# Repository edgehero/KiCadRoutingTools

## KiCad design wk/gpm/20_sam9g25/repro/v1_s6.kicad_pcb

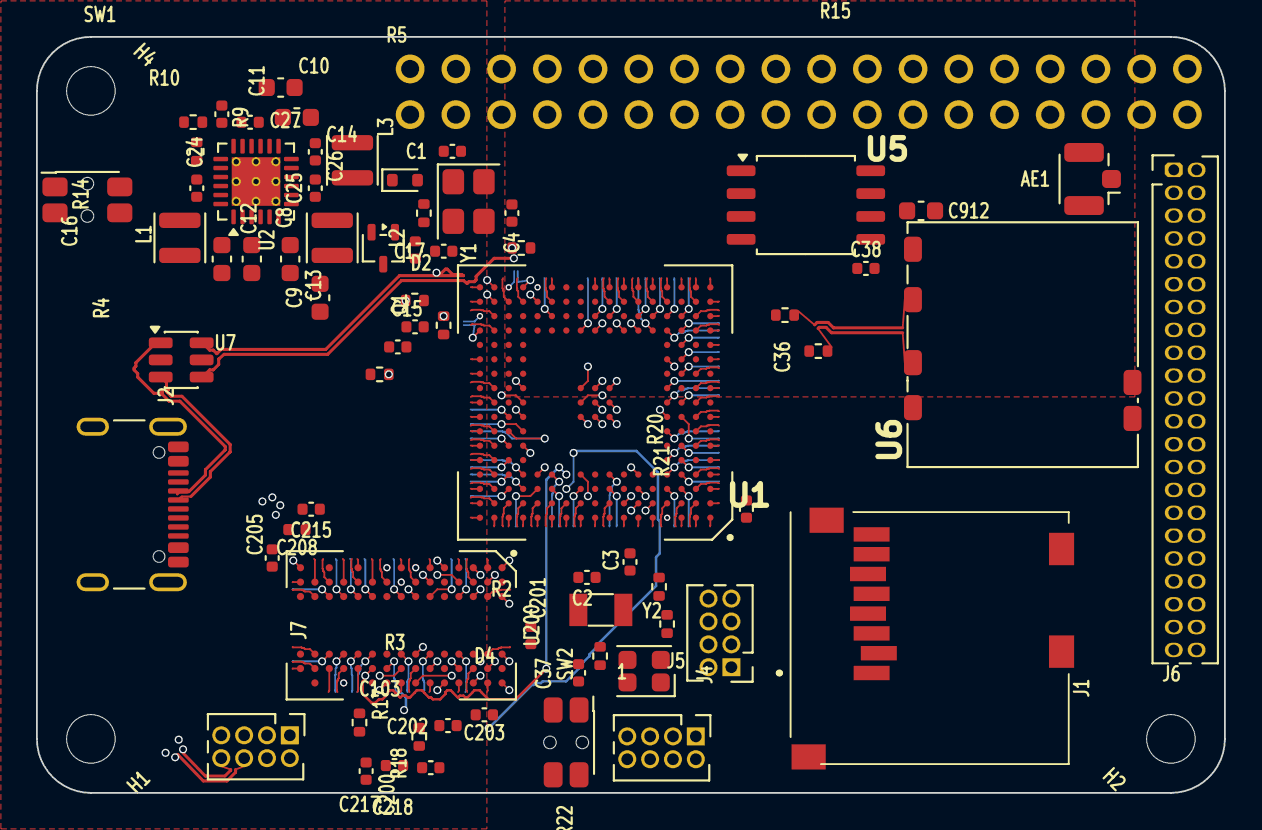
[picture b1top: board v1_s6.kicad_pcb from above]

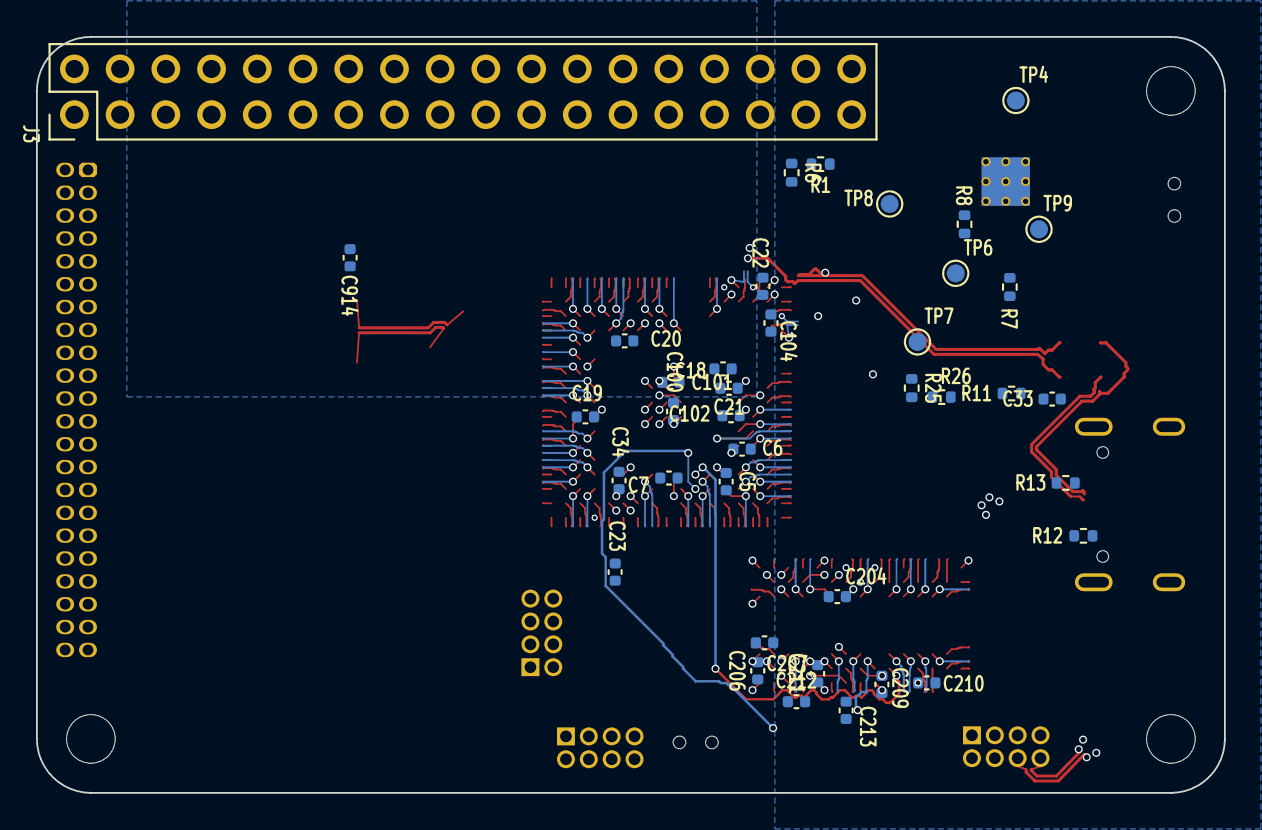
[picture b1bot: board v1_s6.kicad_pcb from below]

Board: 4 copper layers, 66.0 x 42.0 mm, 111 parts (39 on the bottom side), 156 nets.

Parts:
AE1: Antenna_Shield; U.FL_Hirose_U.FL-R-SMT-1_Vertical
C1, C4: 22pF; C_0402_1005Metric
C2, C3: 12pF; C_0402_1005Metric
C5, C6, C7, C17, C18, C19, C20, C21, C22, C23, C24, C25, C26, C27, C100, C101, C102, C103, C104: 220nF; C_0402_1005Metric
C8, C9, C10, C12, C13, C14, C912: 10uF; C_0603_1608Metric
C11, C15: 2.2uF; C_0402_1005Metric
C16: 10pF; C_0402_1005Metric
C33, C34, C38, C200, C201, C202, C203, C204, C205, C206, C207, C208, C209, C210, C211, C212, C213, C215, C217, C218, C914: 100nF; C_0402_1005Metric
C36, C37: 1uF; C_0402_1005Metric
D2: D_Schottky; D_SOD-523
D4: LED_BAGR; LED_RGB_Optosupply_OSTB0805C1E-A-0.8T
H1, H2, H4: MountingHole; MountingHole_2.7mm
J1: Micro_SD_Card_Det; MEM20610118800A
J2: USB_C_Receptacle_USB2.0_16P; USB_C_Receptacle_GCT_USB4105-xx-A_16P_TopMnt_Horizontal
J3: Conn_02x18_Odd_Even; PinHeader_2x18_P2.54mm_Vertical
J4, J5, J7: Conn_01x08; PinHeader_2x04_P1.27mm_Vertical
J6: Conn_02x22_Odd_Even; PinHeader_2x22_P1.27mm_Vertical
L1, L2, L3: 2.2uH; L_Wuerth_MAPI-2512
Q1: BSS84; SOT-323_SC-70
R1, R6, R8, R25, R26: 68k; R_0402_1005Metric
R2, R3, R4, R5, R15, R16: 39; R_0402_1005Metric
R7: 1M; R_0402_1005Metric
R9: 22k; R_0402_1005Metric
R10: 191k; R_0402_1005Metric
R11: 2.2K; R_0402_1005Metric
R12, R13: 5.1K; R_0402_1005Metric
R14: 6k8; R_0402_1005Metric
R17, R18: 2.2k; R_0402_1005Metric
R20, R21, R22: 180; R_0402_1005Metric
SW1, SW2: SW_SPST; SW_SPST_EVQP7C
TP4, TP6, TP7, TP8, TP9: TestPoint; TestPoint_Pad_D1.0mm
U1: AT91SAM9G15; AT91SAM9G10
U2: MCP16501A; QFN-24-1EP_4x4mm_P0.5mm_EP2.7x2.7mm_ThermalVias
U5: W25Q128JVS; SOIC-8_5.23x5.23mm_P1.27mm
U6: RTL8188CUS
U7: USBLC6-2P6; SOT-23-6
U200: DDR2-x16; BGA-84_9x15_8.0x12.5mm
Y1: 12MHz; Crystal_SMD_3225-4Pin_3.2x2.5mm
Y2: 32.768kHz; Crystal_SMD_3215-2Pin_3.2x1.5mm

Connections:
+1V0_LDO: C11.1, C15.1, C103.1, C104.1, R9.1, U1.R12 (VDDPLLA), U1.T17 (VDDUTMIC), U2.18 (LOUT)
/IO expansions/cc1: J2.A5 (CC1), R13.1
/IO expansions/cc2: J2.B5 (CC2), R12.1
/IO expansions/usb-a+: J2.A6 (D+), J2.B6 (D+), U7.3 (I/O2)
/IO expansions/usb-a-: J2.A7 (D-), J2.B7 (D-), U7.1 (I/O1)
/cpu/hse_in: C1.1, U1.T12 (XIN), Y1.1
/cpu/hse_out: C4.1, U1.U12 (XOUT), Y1.3
/cpu/lse_in: C2.1, U1.A6 (XIN32), Y2.1
/cpu/lse_out: C3.1, U1.A5 (XOUT32), Y2.2
/memory/ddr-a2: U1.H15 (A2), U200.M8 (A0)
/memory/ddr-a3: U1.H17 (A3), U200.M3 (A1)
/memory/ddr-a4: U1.G17 (A4), U200.M7 (A2)
/memory/ddr-a5: U1.G16 (A5), U200.N2 (A3)
/memory/ddr-a6: U1.F17 (A6), U200.N8 (A4)
/memory/ddr-a7: U1.E17 (A7), U200.N3 (A5)
/memory/ddr-a8: U1.F16 (A8), U200.N7 (A6)
/memory/ddr-a9: U1.G15 (A9), U200.P2 (A7)
/memory/ddr-a10: U1.G14 (A10), U200.P8 (A8)
/memory/ddr-a11: U1.F15 (A11), U200.P3 (A9)
/memory/ddr-a13: U1.C17 (A13), U200.P7 (A11)
/memory/ddr-a14: U1.E16 (A14), U200.R2 (A12)
/memory/ddr-a15: U1.D16 (A15), U200.R8 (A13)
/memory/ddr-ba0: U1.C16 (A16/BA0), U200.L2 (BA0)
/memory/ddr-ba1: U1.B17 (A17/BA1), U200.L3 (BA1)
/memory/ddr-ba2: U1.E15 (A18), U200.L1 (BA2)
/memory/ddr-cas: U1.C10 (CAS), U200.L7 (~CAS)
/memory/ddr-ck+: U1.C11 (~SDCK), U200.J8 (CK)
/memory/ddr-ck-: U1.D11 (SDCK), U200.K8 (~CK)
/memory/ddr-cke: U1.B12 (SDCKE), U200.K2 (CKE)
/memory/ddr-cs: U1.B8 (NCS1/SDCS), U200.L8 (~CS)
/memory/ddr-d0: U1.D14 (D0), U200.G8 (DQ0)
/memory/ddr-d1: U1.D15 (D1), U200.H3 (DQ3)
/memory/ddr-d2: U1.A16 (D2), U200.F1 (DQ6)
/memory/ddr-d3: U1.B16 (D3), U200.G2 (DQ1)
/memory/ddr-d4: U1.A17 (D4), U200.H1 (DQ4)
/memory/ddr-d5: U1.B15 (D5), U200.H7 (DQ2)
/memory/ddr-d6: U1.C14 (D6), U200.H9 (DQ5)
/memory/ddr-d7: U1.B14 (D7), U200.F9 (DQ7)
/memory/ddr-d8: U1.A15 (D8), U200.D1 (DQ12)
/memory/ddr-d9: U1.C15 (D9), U200.B1 (DQ14)
/memory/ddr-d10: U1.D12 (D10), U200.B9 (DQ15)
/memory/ddr-d11: U1.C13 (D11), U200.D3 (DQ11)
/memory/ddr-d12: U1.A14 (D12), U200.C2 (DQ9)
/memory/ddr-d13: U1.B13 (D13), U200.D7 (DQ10)
/memory/ddr-d14: U1.A13 (D14), U200.C8 (DQ8)
/memory/ddr-d15: U1.C12 (D15), U200.D9 (DQ13)
/memory/ddr-dqm0: U1.A10 (DQM0), U200.F3 (LDM)
/memory/ddr-dqm1: U1.B10 (DQM1), U200.B3 (UDM)
/memory/ddr-dqs0: U1.A11 (DQS0), U200.F7 (LDQS)
/memory/ddr-dqs1: U1.A9 (DQS1), U200.B7 (UDQS)
/memory/ddr-ras: U1.B11 (RAS), U200.K7 (~RAS)
/memory/ddr-sda10: U1.C8 (SDA10), U200.M2 (A10/AP)
/memory/ddr-sdwe: U1.A12 (SDWE), U200.K3 (~WE)
/power/vbg: C16.1, R14.1, U1.U17 (VBG)
ACIN: D2.2 (A), J3.3, Q1.1 (G), R1.1
AC_DET: R1.2, R6.1, U1.T7 (PA24)
BTN_USR: C37.1, SW2.1 (A), U1.J17 (PD19)
CAN0-RX: J3.30, U1.R4 (PA6)
CAN0-TX: J3.29, U1.R1 (PA5)
DDR_VREF: C200.1, C217.2, C218.1, R17.2, R18.1, U200.J2 (VREF)
GND: AE1.2 (Shield), C1.2, C2.2, C3.2, C4.2, C5.2, C6.2, C7.2, C8.2, C9.2, C10.2, C11.2, C12.2, C13.2, C14.2, C15.2, C16.2, C17.2, C18.2, C19.2, C20.2, C21.2, C22.2, C23.2, C24.2, C25.2, C26.2, C27.2, C33.2, C34.2, C36.2, C37.2, C38.2, C100.2, C101.2, C102.2, C103.2, C104.2, C200.2, C201.2, C202.2, C203.2, C204.2, C205.2, C206.2, C207.2, C208.2, C209.2, C210.2, C211.2, C212.2, C213.2, C215.2, C218.2, C912.2, C914.2, J1.G1 (SHIELD), J1.G2 (SHIELD), J1.P6 (VSS), J2.A1 (GND), J2.A12 (GND), J2.B1 (GND), J2.B12 (GND), J2.SH (SHIELD), J3.1, J3.14, J3.23, J3.36, J4.1, J5.1, J6.1, J6.10, J6.11, J6.36, J6.37, J6.44, J7.1, J7.7, R6.2, R10.2, R11.2, R12.2, R13.2, R14.2, R18.2, R26.2, SW1.2 (B), SW2.2 (B), TP4.1 (1_1), U1.B6 (GNDBU), U1.B7 (TST), U1.D6 (GNDANA), U1.H8 (GNDCORE), U1.H9 (GNDIOM), U1.H10 (GNDIOM), U1.J8 (GNDCORE), U1.J9 (GNDIOM), U1.J10 (GNDIOM), U1.J14 (VDDNF), U1.K10 (GNDCORE), U1.M4 (GNDIOP), U1.P6 (GNDIOP), U1.T16 (GNDUTMI), U1.U13 (GNDOSC), U2.4 (LPM), U2.9 (PGND2), U2.10 (PGND3), U2.15 (SELv3), U2.16 (SGND), U2.22 (PGND1), U2.25 (EP), U5.4 (GND), U6.1 (GND), U6.5 (GND), U7.2 (GND), U200.A3 (VSS), U200.A7 (VSSQ), U200.B2 (VSSQ), U200.B8 (VSSQ), U200.D2 (VSSQ), U200.D8 (VSSQ), U200.E3 (VSS), U200.E7 (VSSQ), U200.F2 (VSSQ), U200.F8 (VSSQ), U200.H2 (VSSQ), U200.H8 (VSSQ), U200.J3 (VSS), U200.J7 (VSSDL), U200.K9 (ODT), U200.N1 (VSS), U200.P9 (VSS)
GPIO1: J3.13, U1.T8 (PA25)
GPIO2: J3.20, U1.J16 (PD21)
GPIO3: J3.19, U1.U8 (PA28)
GPIO4: J3.24, U1.K16 (PD20)
GPIOA1: J3.31, U1.A2 (PB13)
GPIOA2: J3.32, U1.C4 (PB14)
GPIOA3: J3.33, U1.C3 (PB15)
GPIOA4: J3.34, U1.A1 (PB16)
GPIOA5: J3.35, U1.B1 (PB17)
I2C-SCL: J3.17, J6.6, U1.U9 (PA31)
I2C-SDA: J3.18, J6.7, U1.R8 (PA30)
LCD-CLK: J6.39, U1.R2 (PC30)
LCD-D2: J6.33, U1.F3 (PC2)
LCD-D3: J6.32, U1.H2 (PC3)
LCD-D4: J6.31, U1.E1 (PC4)
LCD-D5: J6.30, U1.G4 (PC5)
LCD-D6: J6.29, U1.F2 (PC6)
LCD-D7: J6.28, U1.F1 (PC7)
LCD-D10: J6.25, U1.G2 (PC10)
LCD-D11: J6.24, U1.H3 (PC11)
LCD-D12: J6.23, U1.J3 (PC12)
LCD-D13: J6.22, U1.L2 (PC13)
LCD-D14: J6.21, U1.H1 (PC14)
LCD-D15: J6.20, U1.J2 (PC15)
LCD-D18: J6.17, U1.K2 (PC18)
LCD-D19: J6.16, U1.N3 (PC19)
LCD-D20: J6.15, U1.K1 (PC20)
LCD-D21: J6.14, U1.M3 (PC21)
LCD-D22: J6.13, U1.P3 (PC22)
LCD-D23: J6.12, U1.J4 (PC23)
LCD-DE: J6.38, U1.N1 (PC29)
LCD-HSYNC: J6.40, U1.K4 (PC28)
LCD-PWM: J6.42, U1.P2 (PC26)
LCD-VSYNC: J6.41, U1.M1 (PC27)
LED-BLUE: R22.1, U1.T6 (PA21)
LED-GREEN: R21.1, U1.A3 (PB11)
LED-RED: R20.1, U1.B4 (PB12)
MCI0-CK: J1.P5 (CLK), U1.R5 (PA17)
MCI0-D0: J1.P7 (DAT0), U1.U4 (PA15)
MCI0-D1: J1.P8 (DAT1), U1.U5 (PA18)
MCI0-D2: J1.P1 (DAT2), U1.T5 (PA19)
MCI0-D3: J1.P2 (DAT3/CD), U1.U6 (PA20)
MCI0-DC: J1.P3 (CMD), U1.P5 (PA16)
MCI0-DET: J1.CD1 (DET_A), J1.CD2 (DET_B), U1.R9 (PA29)
unnamed: AE1.1 (A), U6.6 (ANT)
unnamed: D4.1 (BK), R22.2
unnamed: D4.3 (GK), R21.2
unnamed: D4.4 (RK), R20.2
unnamed: R3.2, U1.T15 (HFSDMA)
unnamed: R5.2, U1.P16 (HFSDMB)
unnamed: R16.2, U1.M17 (HFSDMC)
unnamed: R2.2, U1.T14 (HFSDPA)
unnamed: R4.2, U1.R16 (HFSDPB)
unnamed: R15.2, U1.L17 (HFSDPC)
unnamed: R9.2, R10.1, U2.19 (LFB)
unnamed: L1.1, U2.23 (SW1)
unnamed: L2.1, U2.8 (SW2)
unnamed: L3.1, U2.11 (SW3)
PWR_BTN: SW1.1 (A), U2.14 (~STRT)
RMII-MDC: J4.8, U1.B3 (PB6)
RMII-MDIO: J5.8, U1.E3 (PB5)
RMII-RX0: J4.4, U1.D3 (PB0)
RMII-RX1: J4.5, U1.D4 (PB1)
RMII-RXDV: J4.2, U1.E4 (PB3)
RMII-RXER: J4.3, U1.D2 (PB2)
RMII-TX0: J5.4, U1.C1 (PB9)
RMII-TX1: J5.5, U1.B2 (PB10)
RMII-TXCK: J5.2, U1.D1 (PB4)
RMII-TXEN: J5.3, U1.C2 (PB7)
SHDN: R7.2, U1.D8 (SHDN), U2.3 (PWRHLD)
SPI0-CLK: J3.25, U1.T4 (PA13), U5.6 (CLK)
SPI0-CS0: U1.U2 (PA14), U5.1 (~CS)
SPI0-MISO: J3.28, U1.U1 (PA11), U5.5 (DI(IO0))
SPI0-MOSI: J3.27, U1.T2 (PA12), U5.2 (DO(IO1))
SPI-CS: J3.26, U1.R6 (PA22)
UART0-RX: J3.12, U1.U3 (PA9)
UART0-TX: J3.11, U1.T1 (PA10)
UART1-RX: J3.16, U1.P4 (PA8)
UART1-TX: J3.15, U1.R3 (PA7)
UART2-RX: J3.22, U1.P1 (PA1)
UART2-TX: J3.21, U1.L3 (PA0)
USB0-D+: R2.1, U1.U14 (HHSDPA), U7.4 (I/O2)
USB0-D-: R3.1, U1.U15 (HHSDMA), U7.6 (I/O1)
USB1-D+: R15.1, U6.2 (USB_DP)
USB1-D-: R16.1, U6.3 (USB_DM)
USB2-D+: J7.8, R4.1, U1.R17 (HHSDPB)
USB2-D-: J7.6, R5.1, U1.P17 (HHSDMB)
USB_DET: R25.2, R26.1, U1.U7 (PA23)
VBUS: C33.1, J2.A4 (VBUS), J2.A9 (VBUS), J2.B4 (VBUS), J2.B9 (VBUS), Q1.3 (D), R11.1, R25.1, U7.5 (VBUS)
VDD-IO: C8.1, C12.1, C17.1, C18.1, C19.1, C20.1, C21.1, C22.1, C23.1, C34.1, C36.1, C38.1, C912.1, C914.1, D4.2 (A), J1.P4 (VDD), J3.2, J6.8, J6.43, L1.2, R7.1, R8.1, TP9.1 (1_1), U1.A4 (ADVREF), U1.B5 (VDDBU), U1.C6 (VDDANA), U1.H4 (VDDIOP1), U1.K14 (VDDNF), U1.P7 (VDDIOP0), U1.P9 (BMS), U1.T13 (VDDOSC), U1.U16 (VDDUTMII), U2.1 (OUT1), U5.8 (VCC), U6.4 (+3V3)
VDD_CORE: C10.1, C14.1, C100.1, C101.1, C102.1, L3.2, TP7.1 (1_1), U1.H14 (VDDCORE), U1.K8 (VDDCORE), U1.K9 (VDDCORE), U2.13 (OUT3)
VDD_DDR: C5.1, C6.1, C7.1, C9.1, C13.1, C201.1, C202.1, C203.1, C204.1, C205.1, C206.1, C207.1, C208.1, C209.1, C210.1, C211.1, C212.1, C213.1, C215.1, C217.1, L2.2, R17.1, TP6.1 (1_1), U1.D10 (VDDIOM), U1.D13 (VDDIOM), U1.F14 (VDDIOM), U2.6 (OUT2), U200.A1 (VDD), U200.A9 (VDDQ), U200.C1 (VDDQ), U200.C3 (VDDQ), U200.C7 (VDDQ), U200.C9 (VDDQ), U200.E1 (VDD), U200.E9 (VDDQ), U200.G1 (VDDQ), U200.G3 (VDDQ), U200.G7 (VDDQ), U200.G9 (VDDQ), U200.J1 (VDDL), U200.J9 (VDD), U200.M9 (VDD), U200.R1 (VDD)
VIN: C24.1, C25.1, C26.1, C27.1, D2.1 (K), Q1.2 (S), TP8.1 (1_1), U2.7 (PVIN2), U2.12 (PVIN3), U2.17 (VIN), U2.20 (SELv2), U2.21 (LEN), U2.24 (PVIN1)
WKUP: R8.2, U1.A7 (WKUP), U2.5 (~STRTO)
~RST: J3.7, U1.P10 (NRST), U2.2 (~RSTO)

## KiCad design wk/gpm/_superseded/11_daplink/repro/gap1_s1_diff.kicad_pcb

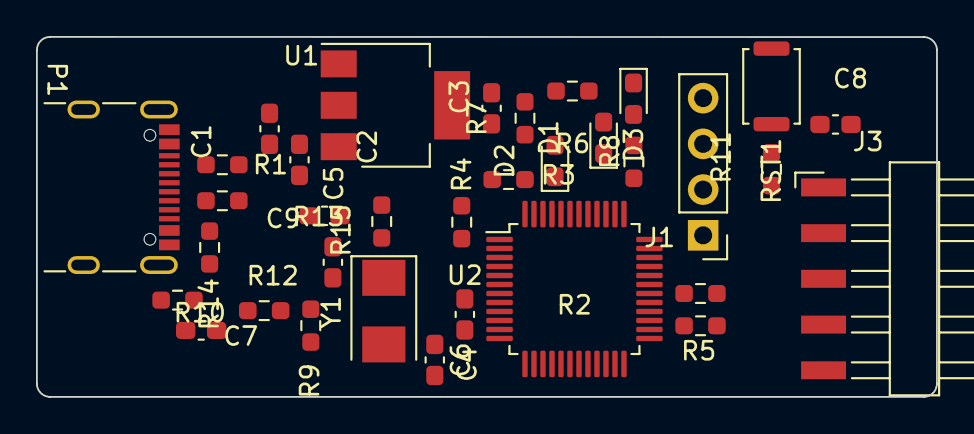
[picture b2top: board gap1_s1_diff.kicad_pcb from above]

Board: 2 copper layers, 50.0 x 20.0 mm, 35 parts (1 on the bottom side), 29 nets, no tracks yet.

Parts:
C1, C4, C8: 10nF; C_0603_1608Metric_Pad1.08x0.95mm_HandSolder
C2, C3: 10uF; C_0603_1608Metric_Pad1.08x0.95mm_HandSolder
C5, C6: 20pF; C_0603_1608Metric_Pad1.08x0.95mm_HandSolder
C7, C9: 18pF; C_0603_1608Metric_Pad1.08x0.95mm_HandSolder
D1: LEDG; LED_0603_1608Metric_Pad1.05x0.95mm_HandSolder
D2: LEDB; LED_0603_1608Metric_Pad1.05x0.95mm_HandSolder
D3: LEDR; LED_0603_1608Metric_Pad1.05x0.95mm_HandSolder
J1: Conn_01x04; PinHeader_1x04_P2.54mm_Vertical
J2, J3: Conn_01x05; Harwin_M20-89005xx_1x05_P2.54mm_Horizontal
P1: USB_C_Receptacle_USB2.0; USB_C_Receptacle_GCT_USB4105-xx-A_16P_TopMnt_Horizontal
R1, R14: 5K1; R_0603_1608Metric_Pad0.98x0.95mm_HandSolder
R2, R3, R4, R11: 10K; R_0603_1608Metric_Pad0.98x0.95mm_HandSolder
R5: 100; R_0603_1608Metric_Pad0.98x0.95mm_HandSolder
R6, R7, R15: 1K5; R_0603_1608Metric_Pad0.98x0.95mm_HandSolder
R8: 470; R_0603_1608Metric_Pad0.98x0.95mm_HandSolder
R9, R10: 4K7; R_0603_1608Metric_Pad0.98x0.95mm_HandSolder
R12, R13: 33; R_0603_1608Metric_Pad0.98x0.95mm_HandSolder
RST1: RST; SW_Push_SPST_NO_Alps_SKRK
U1: AMS1117-3.3; SOT-223-3_TabPin2
U2: STM32F103CBTx; LQFP-48_7x7mm_P0.5mm
Y1: 8MHz; Crystal_SMD_5032-2Pin_5.0x3.2mm

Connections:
+3.3V: C3.1, J1.1, J2.5, J3.1, R2.1, R6.1, R7.1, R9.1, R11.1, R15.2, U1.2 (VO), U2.1 (VBAT), U2.9 (VDDA), U2.24 (VDD), U2.36 (VDD), U2.48 (VDD)
+5V: C1.1, C2.1, P1.A4 (VBUS), P1.A9 (VBUS), P1.B4 (VBUS), P1.B9 (VBUS), U1.3 (VI)
/D+: P1.A6 (D+), P1.B6 (D+), R13.2
/D-: P1.A7 (D-), P1.B7 (D-), R12.2
/IF_RST: C4.1, R2.2, U2.7 (NRST)
/IF_SWCLK: J1.3, U2.37 (PA14)
/IF_SWDIO: J1.2, U2.34 (PA13)
/OSCIN: C5.1, U2.5 (PD0), Y1.1
/OSCOUT: C6.1, U2.6 (PD1), Y1.2
/PA0: R9.2, R10.1, U2.10 (PA0)
/PA9: R8.1, U2.30 (PA9)
/PA11: C7.1, R12.1, U2.32 (PA11)
/PA12: C9.1, R13.1, R15.1, U2.33 (PA12)
/PB5: D1.1 (K), U2.41 (PB5)
/PB6: D2.1 (K), U2.42 (PB6)
/TGT_RST: C8.1, J3.4, R11.2, RST1.1, U2.18 (PB0)
/TGT_RX: J2.3, U2.12 (PA2)
/TGT_SWCLK: J3.3, U2.15 (PA5), U2.26 (PB13)
/TGT_SWDIO: J3.2, R5.1, U2.27 (PB14)
/TGT_TX: J2.4, U2.13 (PA3)
GND: C1.2, C2.2, C3.2, C4.2, C5.2, C6.2, C7.2, C8.2, C9.2, D3.1 (K), J1.4, J2.1, J3.5, P1.A1 (GND), P1.A12 (GND), P1.B1 (GND), P1.B12 (GND), P1.S1 (SHIELD), R1.2, R3.1, R4.1, R10.2, R14.2, RST1.2, U1.1 (GND), U2.8 (VSSA), U2.20 (PB2), U2.23 (VSS), U2.35 (VSS), U2.47 (VSS)
unnamed: D1.2 (A), R6.2
unnamed: D2.2 (A), R7.2
unnamed: D3.2 (A), R8.2
unnamed: P1.A5 (CC1), R1.1
unnamed: P1.B5 (CC2), R14.1
unnamed: R3.2, U2.44 (BOOT0)
unnamed: R5.2, U2.25 (PB12)
unnamed: R4.2, U2.2 (PC13)

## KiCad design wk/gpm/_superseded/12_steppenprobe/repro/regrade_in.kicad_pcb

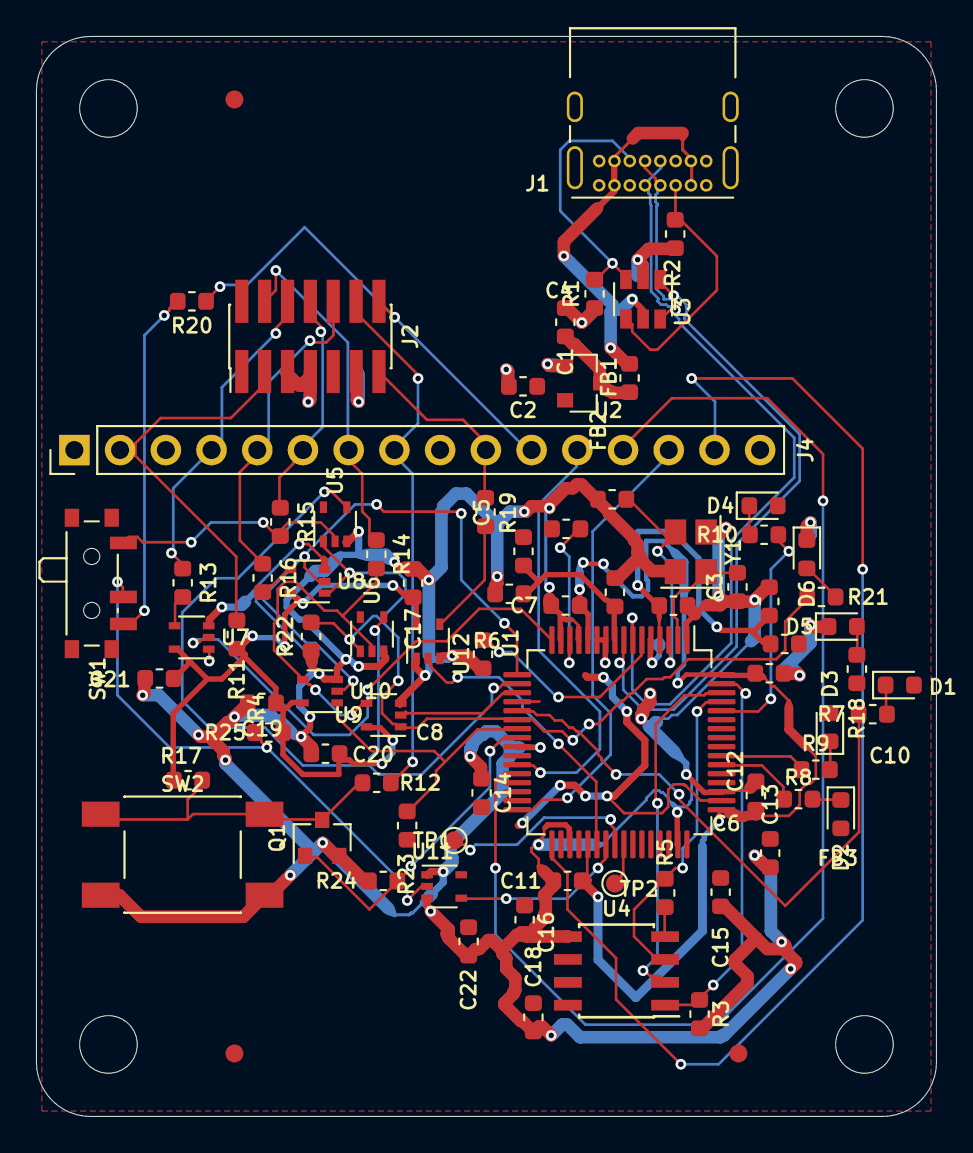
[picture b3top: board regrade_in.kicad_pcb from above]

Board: 2 copper layers, 50.0 x 60.0 mm, 84 parts (0 on the bottom side), 61 nets.

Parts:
C1, C2, C5, C6, C7, C17: 4u7; C_0603_1608Metric
C3, C4: 27pF; C_0603_1608Metric
C8, C9, C10, C11, C12, C13, C14, C15, C16, C18, C19, C20, C21, C22: 100nF; C_0603_1608Metric
D1, D2, D3, D4, D5, D6: LED; LED_0603_1608Metric
FB1, FB2, FB3: Ferrite_Bead; L_0603_1608Metric
FID1, FID2, FID3: Fiducial; Fiducial_1mm_Mask2mm
H1, H2, H3, H4: MountingHole; MountingHole_3.2mm_M3
J1: USB_C_Receptacle_USB2.0; USB_C_Receptacle_GCT_USB4085
J2: Conn_ST_STDC14; PinHeader_2x07_P1.27mm_Vertical_SMD
J4: Conn_01x16; PinHeader_1x16_P2.54mm_Vertical
Q1: 2N7002; SOT-23
R1, R2: 5k1; R_0603_1608Metric
R3, R6, R17, R22, R23, R24: 10k; R_0603_1608Metric
R4: 12k; R_0603_1608Metric
R5: 2k; R_0603_1608Metric
R7, R8, R9, R10, R18, R21: 1k; R_0603_1608Metric
R11, R12, R13, R14, R15, R16, R19, R20: 100R; R_0603_1608Metric
R25: 100k; R_0603_1608Metric
SW1: SW_SPDT; SW_SPDT_PCM12
SW2: SW_Push; SW_Push_1P1T_NO_E-Switch_TL3301NxxxxxG
TP1, TP2: TestPoint; TestPoint_Pad_D1.0mm
U1: FT2232HL; LQFP-64_10x10mm_P0.5mm
U2: XC6206PxxxMR; SOT-23
U3: SRV05-4; SOT-23-6
U4: 93LCxxB; SOIC-8_3.9x4.9mm_P1.27mm
U5, U7, U8, U9, U10, U11, U12: 74LVC1G125; SOT-353_SC-70-5
U6: 74LVC1G126; SOT-353_SC-70-5
Y1: Crystal_GND24; Crystal_SMD_3225-4Pin_3.2x2.5mm

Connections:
+1V8: C7.1, C10.1, C11.1, C12.1, U1.12 (VCORE), U1.37 (VCORE), U1.49 (VREGOUT), U1.64 (VCORE)
+3V3: C2.1, C13.1, C14.1, C15.1, C16.1, C18.1, C22.1, D1.2 (A), D2.2 (A), D3.2 (A), D4.2 (A), FB2.2, FB3.2, J4.1, R6.2, R18.1, R23.2, U1.20 (VCCIO), U1.31 (VCCIO), U1.42 (VCCIO), U1.50 (VREGIN), U1.56 (VCCIO), U2.2 (VO), U4.8 (VCC), U5.5 (VCC), U6.5 (VCC), U11.5 (VCC)
+5V: C1.1, FB1.1, U2.3 (VI)
/ACT_LED_K: D1.1 (K), R7.2
/ACT_LED_N: R7.1, U1.21 (ADBUS4)
/CTS_N: TP2.1, U1.41 (BDBUS3)
/EE_CLK: U1.62 (EECLK), U4.2 (SCLK)
/EE_CS: R3.1, U1.63 (EECS), U4.1 (CS)
/EE_DATA: R5.2, U1.61 (EEDATA), U4.3 (DI)
/EE_DO: R5.1, U4.4 (DO)
/GPIO_A: J4.12, U1.27 (ACBUS1)
/GPIO_B: J4.13, U1.28 (ACBUS2)
/GPIO_C: J4.14, U1.32 (ACBUS5)
/GPIO_D: J4.15, U1.33 (ACBUS6)
/OSCI: C3.1, U1.2 (OSCI), Y1.1
/OSCO: C4.1, U1.3 (OSCO), Y1.3
/PWR_LED_A: D5.2 (A), R18.2
/REF: R4.1, U1.6 (REF)
/RESET_N: R6.1, U1.14 (~RESET)
/RTS_N: TP1.1, U1.40 (BDBUS2)
/RXD: U1.39 (BDBUS1), U11.4
/RXD_IN: R25.1, SW1.2 (B), U11.2
/RXD_R: R20.1, SW1.3 (C)
/RXD_TRGT: J2.14 (VCP_TX), J4.11, R20.2
/RX_LED_K: D2.1 (K), R8.1
/RX_LED_N: R8.2, U1.54 (BCBUS3)
/SRST: Q1.1 (G), R24.2, U1.24 (ADBUS7)
/SRST_N_R: Q1.3 (D), R12.2, R17.1, SW2.1
/SRST_N_TRGT: J2.12 (~RST), J4.8, R12.1
/SWDIO_OE_N: R23.1, U1.23 (ADBUS6), U10.1
/SWD_EN: R21.2, R22.2, U1.22 (ADBUS5), U5.1, U6.1, U8.1, U9.1
/SWD_EN_LED: D6.2 (A), R21.1
/TCK: U1.16 (ADBUS0), U7.2
/TCK_R: R13.2, U7.4
/TCK_TRGT: J2.6 (JCLK/SWCLK), J4.4, R13.1
/TDI: U1.17 (ADBUS1), U8.2, U10.2
/TDI_R: R16.2, U8.4
/TDI_TRGT: J2.10 (JTDI/NC), J4.5, R16.1
/TDO: U1.18 (ADBUS2), U5.4, U6.4
/TDO_R: R15.2, SW1.1 (A), U5.2
/TDO_TRGT: J2.8 (JTDO/SWO), J4.6, R15.1
/TMS: U1.19 (ADBUS3), U9.2
/TMS_R: R14.2, U6.2, U9.4, U10.4
/TMS_TRGT: J2.4 (JTMS/SWDIO), J4.7, R14.1
/TXD: U1.38 (BDBUS0), U12.2
/TXD_R: R19.2, U12.4
/TXD_TRGT: J2.13 (VCP_RX), J4.10, R19.1
/TX_LED_K: D3.1 (K), R9.1
/TX_LED_N: R9.2, U1.55 (BCBUS4)
/USB_CC1: J1.A5 (CC1), R2.1, U3.4 (IO3)
/USB_CC2: J1.B5 (CC2), R1.1, U3.3 (IO2)
/USB_DM: J1.A7 (D-), J1.B7 (D-), U1.7 (DM), U3.6 (IO4)
/USB_DP: J1.A6 (D+), J1.B6 (D+), U1.8 (DP), U3.1 (IO1)
/USB_LED_K: D4.1 (K), R10.1
/USB_LED_N: R10.2, U1.60 (~PWREN)
/VDRIVE_TRGT: J2.3 (VCC), J4.2, R11.1
/VPHY: C6.1, C9.1, FB3.1, U1.4 (VPHY)
/VPLL: C5.1, C8.1, FB2.1, U1.9 (VPLL)
GND: C1.2, C2.2, C3.2, C4.2, C5.2, C6.2, C7.2, C8.2, C9.2, C10.2, C11.2, C12.2, C13.2, C14.2, C15.2, C16.2, C17.2, C18.2, C19.2, C20.2, C21.2, C22.2, D5.1 (K), D6.1 (K), J1.A1 (GND), J1.A12 (GND), J1.B1 (GND), J1.B12 (GND), J1.S1 (SHIELD), J2.5 (GND), J2.7 (GND), J2.11 (GNDDetect), J4.3, J4.9, J4.16, Q1.2 (S), R1.2, R2.2, R3.2, R4.2, R22.1, R24.1, SW2.2, U1.1 (GND), U1.5 (GND), U1.10 (AGND), U1.11 (GND), U1.13 (TEST), U1.15 (GND), U1.25 (GND), U1.35 (GND), U1.47 (GND), U1.51 (GND), U2.1 (GND), U3.2 (VN), U4.5 (GND), U5.3 (GND), U6.3 (GND), U7.1, U7.3 (GND), U8.3 (GND), U9.3 (GND), U10.3 (GND), U11.1, U11.3 (GND), U12.1, U12.3 (GND), Y1.2, Y1.4
VBUS: FB1.2, J1.A4 (VBUS), J1.A9 (VBUS), J1.B4 (VBUS), J1.B9 (VBUS), U3.5 (VP)
Vdrive: C17.1, C19.1, C20.1, C21.1, R11.2, R17.2, R25.2, U7.5 (VCC), U8.5 (VCC), U9.5 (VCC), U10.5 (VCC), U12.5 (VCC)

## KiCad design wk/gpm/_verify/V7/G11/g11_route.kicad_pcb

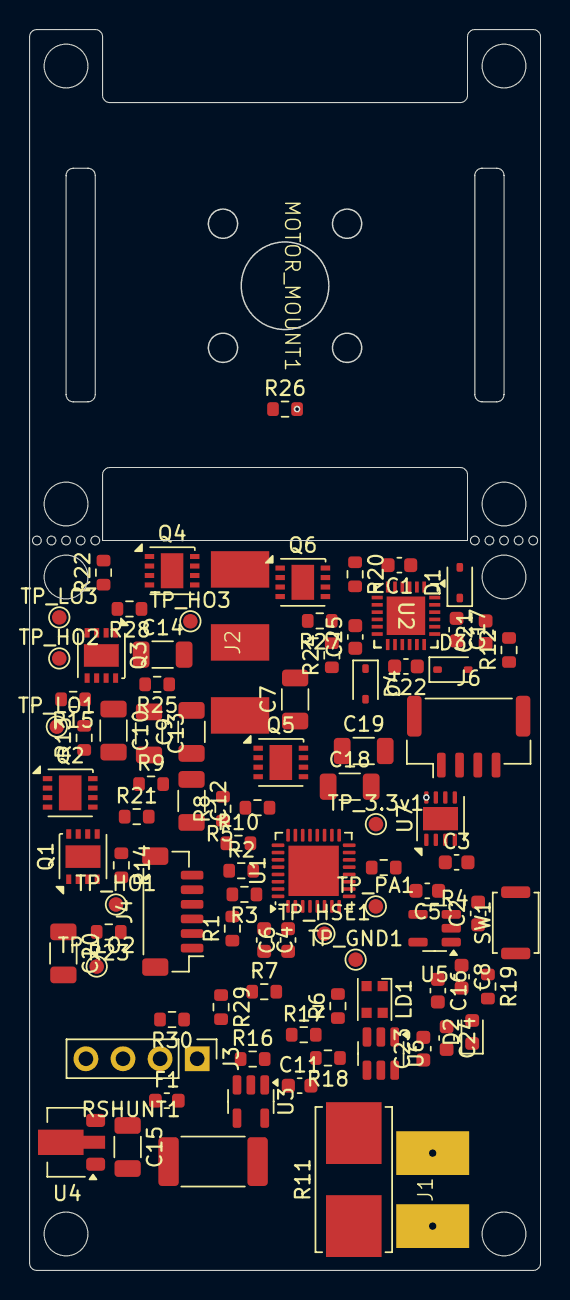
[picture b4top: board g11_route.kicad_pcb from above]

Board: 4 copper layers, 35.0 x 85.0 mm, 93 parts (1 on the bottom side), 55 nets, no tracks yet.

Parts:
C1, C8, C16, C24: 10uF; C_0603_1608Metric
C2, C3, C4, C5, C6, C11, C21, C23: 100nF; C_0603_1608Metric
C7, C9, C10, C12, C13, C14, C15, C18, C19, C20: 22uF; C_1206_3216Metric
C17, C22, C25: 1uF; C_0603_1608Metric
D1, D3, D4: 1N5819WS; D_SOD-323
D2: LED_RED; LED_0603_1608Metric
F1: Fuse; Fuse_0603_1608Metric
J1: NC; 2P_ESC_BAT_PAD_50A_Pitch_5.0mm
J2, J5: NC; 3P_ESC_OUT_50A_5.0mm_Pitch
J3: 2.54mm Pinhead 4P; PinHeader_1x04_P2.54mm_Vertical
J4: SH1.0mm 6P Vertical; JST_SH_BM06B-SRSS-TB_1x06-1MP_P1.00mm_Vertical
J6: GH1.25-4P Vertical; JST_GH_BM04B-GHS-TBT_1x04-1MP_P1.25mm_Vertical
LD1: WS2812B-2020; LED_WS2812B-2020_PLCC4_2.0x2.0mm
MOTOR_MOUNT1: NC; 1404_4300kv_motor
Q1, Q2, Q3, Q4, Q5, Q6: AON7544; DFN-8-1EP_3x3mm_P0.65mm_EP1.55x2.4mm
R1, R5, R8, R18: 30k; R_0603_1608Metric
R2, R6, R9, R17: 3.6k; R_0603_1608Metric
R3, R4, R7, R10, R12, R13, R20, R21, R24, R25, R26: 10k; R_0603_1608Metric
R11: 30A FUSE; Fuseholder_Littelfuse_Nano2_154x
R14, R15, R22, R23, R27, R28, R29, R30: 22R; R_0603_1608Metric
R16: 100k; R_0603_1608Metric
R19: 330R; R_0603_1608Metric
RSHUNT1: 0.3mR 3W; R_2512_6332Metric_Pad1.40x3.35mm_HandSolder
SW1: SW_Push; SW_Push_SPST_NO_Alps_SKRK
TP_3.3v1: NC; TestPoint_Pad_D1.0mm
TP_GND1: NC; TestPoint_Pad_D1.0mm
TP_HO1, TP_HO2, TP_HO3: NC; TestPoint_Pad_D1.0mm
TP_HSE1: NC; TestPoint_Pad_D1.0mm
TP_LO1, TP_LO2, TP_LO3: NC; TestPoint_Pad_D1.0mm
TP_PA1: NC; TestPoint_Pad_D1.0mm
U1: STM32L431KCUx; QFN-32-1EP_5x5mm_P0.5mm_EP3.45x3.45mm
U2: FD6288Q; QFN24_4X4_SEM
U3: INA169; SOT-23-5
U4: HT75xx-1-SOT89; SOT-89-3
U5: AP2112K-3.3; SOT-23-5
U6: SN74LVC1T45DBV; SOT-23-6
U7: TJA1051TK-3; HVSON-8-1EP_3x3mm_P0.65mm_EP1.6x2.4mm

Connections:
3.3v: C4.2, C5.2, C6.2, C16.1, J4.1, R19.1, TP_3.3v1.1, U1.1 (VDD), U1.5 (VDDA), U1.17 (VDD), U5.5 (VOUT), U6.6 (VCCB)
5v: C1.1, C3.1, C8.1, C21.2, C23.2, C24.1, D1.2 (A), D3.2 (A), D4.2 (A), F1.2, J6.1, LD1.4 (VDD), U2.4 (VCC), U5.1 (VIN), U5.3 (EN), U6.1 (VCCA), U7.3 (VCC), U7.5 (VIO)
ADC1_IN6_TEMP: TP_PA1.1, U1.7 (PA1)
ADC1_IN8_BATTERY_CURRENT: R16.2, U1.9 (PA3), U3.1
ADC1_IN11_BATTERY_VOLTAGE: R17.2, R18.2, U1.12 (PA6)
BAT+: C11.1, R11.2, R18.1, RSHUNT1.2, U3.3 (+), U3.5 (V+)
BAT_IN+: J1.1, R11.1
CAN_H: J6.2, U7.7 (CANH)
CAN_L: J6.3, U7.6 (CANL)
CAN_RX: U1.21 (PA11), U7.4 (RXD)
CAN_SILENT: R26.2, U7.8 (S)
CAN_TX: U1.22 (PA12), U7.1 (TXD)
COMP2_INP: R3.1, R7.1, R10.1, U1.27 (PB4)
COMP_INM_A: R1.1, R2.2, R3.2, U1.30 (PB7)
COMP_INM_B: R5.1, R6.2, R7.2, U1.11 (PA5)
COMP_INM_C: R8.1, R9.2, R10.2, U1.10 (PA4)
FD6288_HIN1: U1.20 (PA10), U2.22 (HIN1)
FD6288_HIN2: U1.19 (PA9), U2.23 (HIN2)
FD6288_HIN3: U1.18 (PA8), U2.24 (HIN3)
FD6288_HO1: R12.2, R14.1, U2.19 (HO1)
FD6288_HO2: R20.2, R22.1, U2.16 (HO2)
FD6288_HO3: R24.2, R27.1, U2.13 (HO3)
FD6288_LIN1: U1.15 (PB1), U2.1 (LIN1)
FD6288_LIN2: U1.14 (PB0), U2.2 (LIN2)
FD6288_LIN3: U1.13 (PA7), U2.3 (LIN3)
FD6288_LO1: R13.2, R15.1, U2.11 (LO1)
FD6288_LO2: R21.2, R23.1, U2.10 (LO2)
FD6288_LO3: R25.2, R28.1, U2.9 (LO3)
FD6288_VB1: C17.1, D1.1 (K), U2.20 (VB1)
FD6288_VB2: C22.1, D3.1 (K), U2.17 (VB2)
FD6288_VB3: C25.1, D4.1 (K), U2.14 (VB3)
FD6288_VS1: C17.2, J2.1, J5.1, Q1.1 (S), Q2.3 (D), R1.2, U2.18 (VS1)
FD6288_VS2: C22.2, J2.2, J5.2, Q3.1 (S), Q4.3 (D), R5.2, U2.15 (VS2)
FD6288_VS3: C25.2, J2.3, J5.3, Q5.1 (S), Q6.3 (D), R8.2, U2.12 (VS3)
GND: C1.2, C2.1, C3.2, C4.1, C5.1, C6.1, C7.2, C8.2, C9.2, C10.2, C11.2, C12.2, C13.2, C14.2, C15.2, C16.2, C18.2, C19.2, C20.2, C21.1, C23.1, C24.2, D2.1 (K), J1.2, J3.3, J4.6, J6.4, LD1.2 (VSS), Q2.1 (S), Q4.1 (S), Q6.1 (S), R2.1, R4.1, R6.1, R9.1, R12.1, R13.1, R16.1, R17.1, R20.1, R21.1, R24.1, R25.1, R26.1, SW1.1, TP_GND1.1, U1.16 (VSS), U1.32 (VSS), U1.33 (VSS), U2.6 (COM), U3.2 (GND), U4.1 (GND), U5.2 (GND), U6.2 (GND), U6.5 (DIR), U7.2 (GND), U7.9 (GND)
HSE_IN: TP_HSE1.1, U1.6 (PA0)
unnamed: D2.2 (A), R19.2
unnamed: J3.1, R29.2
unnamed: J3.4, J4.2, R30.2
unnamed: LD1.3 (DIN), U6.3 (A)
unnamed: Q1.2 (G), R14.2, TP_HO1.1
unnamed: Q2.2 (G), R15.2, TP_LO1.1
unnamed: Q3.2 (G), R22.2, TP_HO2.1
unnamed: Q4.2 (G), R23.2, TP_LO2.1
unnamed: Q5.2 (G), R27.2, TP_HO3.1
unnamed: Q6.2 (G), R28.2, TP_LO3.1
unnamed: R4.2, U1.31 (PH3)
unnamed: C15.1, F1.1, U4.3 (VOUT)
ST_NRST: C2.2, SW1.2, U1.4 (NRST)
ST_SWCLK: J4.5, U1.24 (PA14)
ST_SWDIO: J4.4, U1.23 (PA13)
TIM15_CH1: R29.1, U1.8 (PA2)
USART1_TX: R30.1, U1.29 (PB6)
VDD: C7.1, C9.1, C10.1, C12.1, C13.1, C14.1, C18.1, C19.1, C20.1, Q1.3 (D), Q3.3 (D), Q5.3 (D), RSHUNT1.1, U3.4 (-), U4.2 (VIN)
WS2812_SIGNAL: U1.26 (PB3), U6.4 (B)

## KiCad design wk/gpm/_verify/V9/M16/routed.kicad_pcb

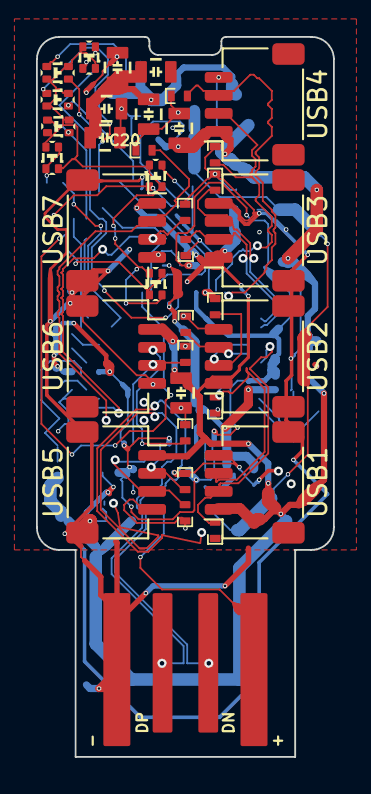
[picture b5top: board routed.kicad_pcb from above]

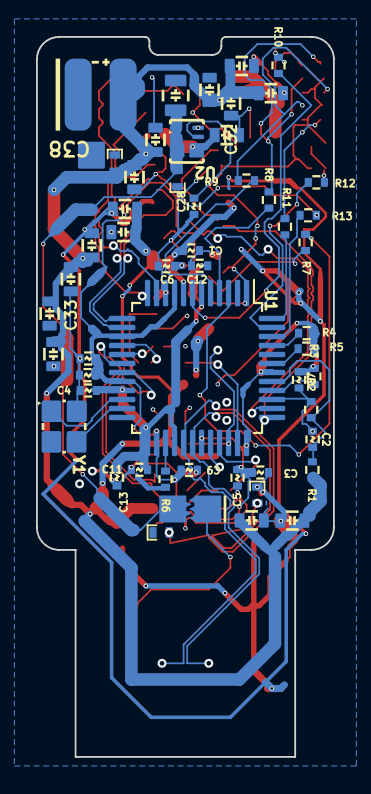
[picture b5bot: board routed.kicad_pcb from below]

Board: 2 copper layers, 16.5 x 40.0 mm, 90 parts (53 on the bottom side), 45 nets.

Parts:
C1: 1uF 10V; 1005_C
C2, C5, C6, C7, C8, C9, C10, C11, C12, C13: 0.1uF; 1005_C
C3, C4: 10uF 6.3V; 1005_C
C14, C15, C16, C17, C18, C19, C20, C21: 0.1uF 100V; 2012_C
C22, C23, C24, C25, C26, C27, C29, C30, C31, C32, C33, C34, C35, C36, C37: 22uF 10V; 1608_C
C28: 15nF; 1005_C
C38: 330uF 10V; CP_Elec_6.3x11_Board_Edge_Mirrored
D1, D2, D3, D4, D5, D6, D7, D8, D9, D10, D11, D12, D13, D14, D22, D23: TVS; D_0402
D15, D16, D17, D18, D19, D20, D21: USB; Duo_LED_1.6x0.8_Kingbright_APHB1608LZGKSURKC
D24, D25: 5V; D_0402
H1: Strap; Plain_Hole_3mm
J1: HOST; USB_A_PCB_traces_small
J2: USB1; JST_SH_SM04B-SRSS-TB_1x04-1MP_P1.00mm_Horizontal
J3: USB2; JST_SH_SM04B-SRSS-TB_1x04-1MP_P1.00mm_Horizontal
J4: USB3; JST_SH_SM04B-SRSS-TB_1x04-1MP_P1.00mm_Horizontal
J5: USB4; JST_SH_SM04B-SRSS-TB_1x04-1MP_P1.00mm_Horizontal
J6: USB5; JST_SH_SM04B-SRSS-TB_1x04-1MP_P1.00mm_Horizontal
J7: USB6; JST_SH_SM04B-SRSS-TB_1x04-1MP_P1.00mm_Horizontal
J8: USB7; JST_SH_SM04B-SRSS-TB_1x04-1MP_P1.00mm_Horizontal
J9: EXTGND; 1P-1.5x1.5
JP1: EXTPWR; JP-2_1.5x1.5
R1: 10k; R_1005_C
R2, R3, R4, R5: 100k; R_1005_C
R6: 2.7k; R_1005_C
R7, R8, R9, R10, R11, R12, R13: 470; R_1005_C
U1: MaxLinear_XR22417-48; LQFP-48_7x7mm_P0.5mm
U2: Dialog_SLG5NT1487V; TDFN-8_1.5x2mm_Fused-Lead_JEDEC_MO-252_W2015D
Y1: 12MHz 50ppm 16-20pF; Crystal_4-SMD_2.5x2mm

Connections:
+1V8: C4.1, C11.1, C12.1, C13.1, U1.6 (VCC18), U1.21 (VCC18), U1.25 (1V8_OUT), U1.28 (VCC18)
+3.3V: C3.1, C5.1, C6.1, C7.1, C8.1, C9.1, C10.1, R3.1, R4.1, R5.1, U1.9 (3V3_OUT), U1.15 (VCC33), U1.20 (VCC33), U1.26 (VCC33), U1.31 (VCC33), U1.36 (VCC33), U1.42 (VCC33)
+5V: C1.1, C14.1, C15.1, C16.1, C17.1, C18.1, C19.1, C20.1, C22.1, C23.1, C24.1, C25.1, C26.1, C27.1, C29.1, C30.1, C31.1, C32.1, C33.1, C34.1, C35.1, C36.1, C37.1, C38.1 (+), D25.2 (A2), J2.1, J3.1, J4.1, J5.1, J6.1, J7.1, J8.1, R1.1, U1.8 (VCC5), U2.5 (S)
/D+: D23.2 (A2), J1.3, U1.30 (UP_D+)
/D-: D22.2 (A2), J1.2, U1.29 (UP_D-)
/LC: D15.GK (2), D15.RA (3), D16.GK (2), D16.RA (3), D17.GK (2), D17.RA (3), D18.GK (2), D18.RA (3), D19.GK (2), D19.RA (3), D20.GK (2), D20.RA (3), D21.GK (2), D21.RA (3), U1.1 (LED_CTL)
/LED1: R7.2, U1.3 (LED1/SCL)
/LED2: R8.2, U1.4 (LED2)
/LED3: R9.2, U1.5 (LED3)
/LED4: R10.2, U1.7 (LED4)
/LED5: R11.2, U1.48 (LED5)
/LED6: R12.2, U1.47 (LED6)
/LED7: R13.2, U1.46 (LED7)
/U1D+: D2.2 (A2), J2.3, U1.19 (USB1D+)
/U1D-: D1.2 (A2), J2.2, U1.18 (USB1D-)
/U2D+: D4.2 (A2), J3.3, U1.17 (USB2D+)
/U2D-: D3.2 (A2), J3.2, U1.16 (USB2D-)
/U3D+: D6.2 (A2), J4.3, U1.14 (USB3D+)
/U3D-: D5.2 (A2), J4.2, U1.13 (USB3D-)
/U4D+: D8.2 (A2), J5.3, U1.12 (USB4D+)
/U4D-: D7.2 (A2), J5.2, U1.11 (USB4D-)
/U5D+: D10.2 (A2), J6.3, U1.33 (USB5D+)
/U5D-: D9.2 (A2), J6.2, U1.32 (USB5D-)
/U6D+: D12.2 (A2), J7.3, U1.35 (USB6D+)
/U6D-: D11.2 (A2), J7.2, U1.34 (USB6D-)
/U7D+: D14.2 (A2), J8.3, U1.38 (USB7D+)
/U7D-: D13.2 (A2), J8.2, U1.37 (USB7D-)
/XI: U1.22 (XTALIN), Y1.1
/XO: U1.23 (XTALOUT), Y1.3
GND: C1.2, C2.2, C3.2, C4.2, C5.2, C6.2, C7.2, C8.2, C9.2, C10.2, C11.2, C12.2, C13.2, C14.2, C15.2, C16.2, C17.2, C18.2, C19.2, C20.2, C21.2, C22.2, C23.2, C24.2, C25.2, C26.2, C27.2, C28.2, C29.2, C30.2, C31.2, C32.2, C33.2, C34.2, C35.2, C36.2, C37.2, C38.2 (-), D1.1 (A1), D2.1 (A1), D3.1 (A1), D4.1 (A1), D5.1 (A1), D6.1 (A1), D7.1 (A1), D8.1 (A1), D9.1 (A1), D10.1 (A1), D11.1 (A1), D12.1 (A1), D13.1 (A1), D14.1 (A1), D22.1 (A1), D23.1 (A1), D24.1 (A1), D25.1 (A1), J1.4, J2.4, J2.MP (MountPin), J3.4, J3.MP (MountPin), J4.4, J4.MP (MountPin), J5.4, J5.MP (MountPin), J6.4, J6.MP (MountPin), J7.4, J7.MP (MountPin), J8.4, J8.MP (MountPin), J9.1, R2.2, R6.2, U1.10 (GND), U1.24 (GND), U1.39 (GND), U2.8 (GND), Y1.2 (GND), Y1.4 (GND)
unnamed: D15.GA (1), D15.RK (4), R7.1
unnamed: D16.GA (1), D16.RK (4), R8.1
unnamed: D17.GA (1), D17.RK (4), R9.1
unnamed: D18.GA (1), D18.RK (4), R10.1
unnamed: D19.GA (1), D19.RK (4), R11.1
unnamed: D20.GA (1), D20.RK (4), R12.1
unnamed: D21.GA (1), D21.RK (4), R13.1
unnamed: J1.1, JP1.1
unnamed: R3.2, U1.40 (EXT_RST#)
unnamed: R6.1, U1.27 (REXT)
unnamed: R5.2, U1.43 (TEST1#)
unnamed: R4.2, U1.45 (TEST3#)
unnamed: C2.1, R1.2, R2.1, U1.41 (VBUS_SENSE)
unnamed: C28.1, U2.7 (CAP)
VIN: C21.1, D24.2 (A2), JP1.2, U2.1 (VDD), U2.2 (ON), U2.3 (D)
